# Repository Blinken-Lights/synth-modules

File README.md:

# synth-modules
Synth module schematics and code

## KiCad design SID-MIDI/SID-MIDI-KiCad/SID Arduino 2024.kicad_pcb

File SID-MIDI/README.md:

Schematic and Arduino code to integrate a SID chip with MIDI notes and CC commands for all parameters.

The schematic is intended for Eurorack, so it uses a ±12V dual supply, and boosts the SID audio output to just over ±5V, Eurorack standard levels. With some modification, this project could be used as the basis for controlling a SID in whatever context you need.

The physical controls (3 knobs and a switch) are basic, because the SID takes up a lot of pins on the Arduino, which doesn't leave many pins available for controls. But you could build a much larger controller and send data to the Arduino via MIDI, or by changing the code, you could increase the serial speed to 250000 baud and send control data even faster.

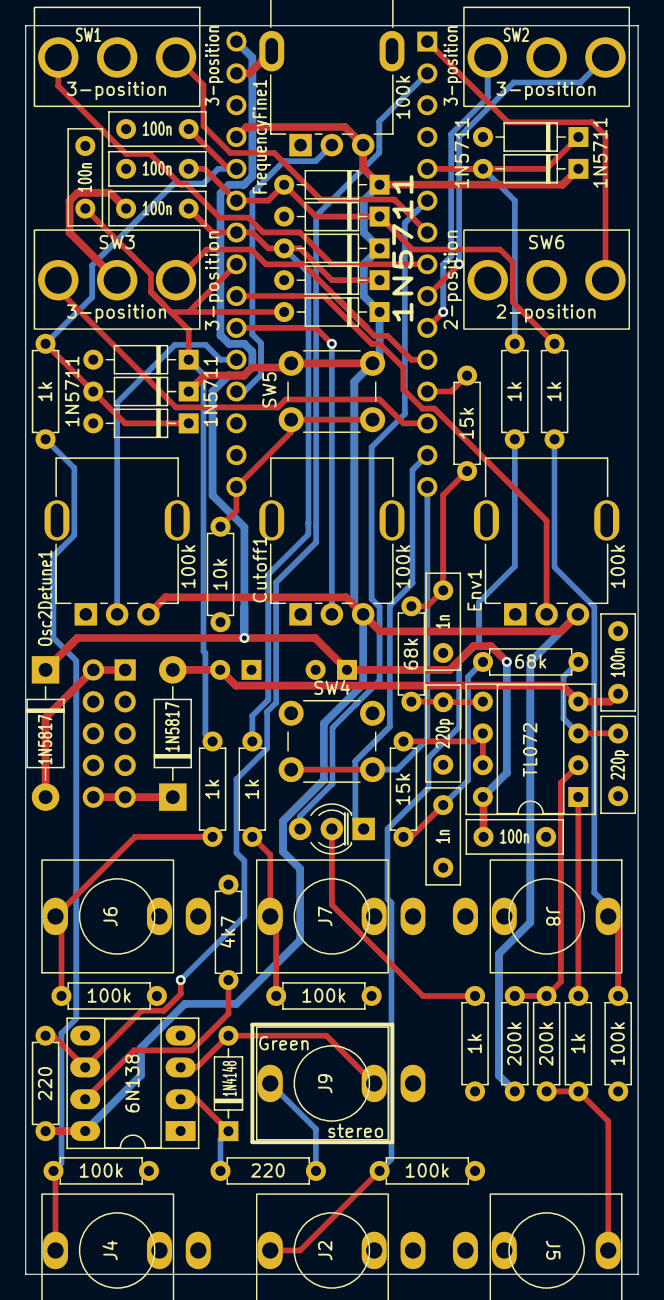
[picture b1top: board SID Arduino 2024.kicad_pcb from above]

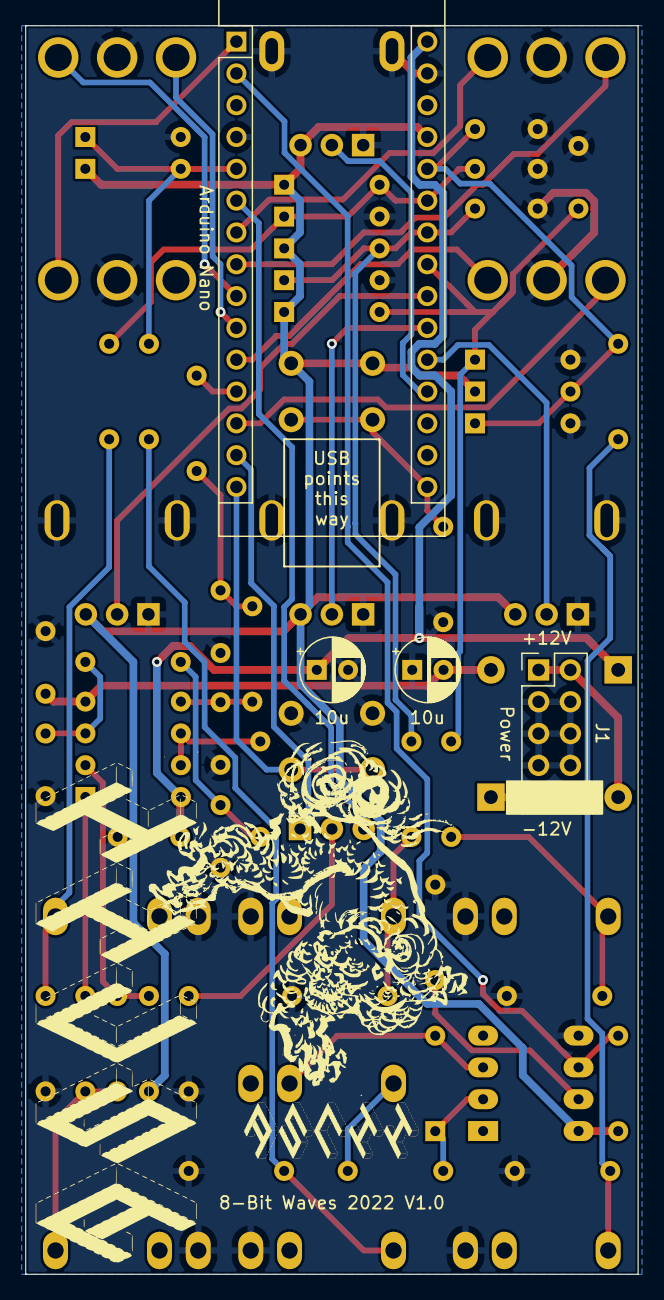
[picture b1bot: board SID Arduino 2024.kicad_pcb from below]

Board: 2 copper layers, 48.9 x 99.7 mm, 69 parts (4 on the bottom side), 46 nets.

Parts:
A1: Arduino_Nano_v3.x; Arduino_Nano
C1, C2: 10u; CP_Radial_D5.0mm_P2.50mm
C3, C4, C7, C8, C9, C10: 100n; C_Disc_D7.5mm_W2.5mm_P5.00mm
C5, C11: 1n; C_Disc_D7.5mm_W2.5mm_P5.00mm
C6, C12: 220p; C_Disc_D7.5mm_W2.5mm_P5.00mm
Cutoff1: 100k; Potentiometer_GND_Alpha_RD901F-40-00D_Single_Vertical_OvalH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
D1, D2: 1N5817; D_DO-41_SOD81_P10.16mm_Horizontal
D3, D4, D8, D9, D10, D11, D12, D13, D14, D15: 1N5711; D_DO-35_SOD27_P7.62mm_Horizontal
D16: 1N4148; D_DO-35_SOD27_P7.62mm_HorizontalVal
D17: Status; LED_D3.0mm-3
Env1: 100k; Potentiometer_GND_Alpha_RD901F-40-00D_Single_Vertical_OvalH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
FrequencyFine1: 100k; Potentiometer_GND_Alpha_RD901F-40-00D_Single_Vertical_OvalH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
J1: Power; PinHeader_2x05_P2.54mm_Vertical
J2: Clk; Thonkiconn
J4: 1V/Oct; Thonkiconn
J5: Audio; Thonkiconn
J6: Detune; Thonkiconn
J7: Cutoff; Thonkiconn
J8: Envelope; Thonkiconn
J9: MIDI; Thonkiconn
Osc2Detune1: 100k; Potentiometer_GND_Alpha_RD901F-40-00D_Single_Vertical_OvalH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
R1, R7, R13, R14, R15: 100k; R_Axial_DIN0207_L6.3mm_D2.5mm_P7.62mm_Horizontal
R2: 10k; R_Axial_DIN0207_L6.3mm_D2.5mm_P7.62mm_Horizontal
R3, R9, R11, R16, R17, R18, R22: 1k; R_Axial_DIN0207_L6.3mm_D2.5mm_P7.62mm_Horizontal
R6, R23: 15k; R_Axial_DIN0207_L6.3mm_D2.5mm_P7.62mm_Horizontal
R8, R24: 68k; R_Axial_DIN0207_L6.3mm_D2.5mm_P7.62mm_Horizontal
R10, R12: 200k; R_Axial_DIN0207_L6.3mm_D2.5mm_P7.62mm_Horizontal
R19, R21: 220; R_Axial_DIN0207_L6.3mm_D2.5mm_P7.62mm_Horizontal
R20: 4k7; R_Axial_DIN0207_L6.3mm_D2.5mm_P7.62mm_Horizontal
SW1: Wave1; toggle switch
SW2: Wave2; toggle switch
SW3: Mix; toggle switch
SW4: Clk; SW_PUSH_6mm
SW5: Learn; SW_PUSH_6mm
SW6: Arp/Sync Type; toggle switch
U1: TL072; DIP-8_W7.62mm_Socket
U2: 6N138; DIP-8_W7.62mm_Socket_LongPads

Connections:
1V/Oct: A1.26 (A7), C7.1, D8.2 (A), D9.1 (K), R9.1
+5V: A1.27 (+5V), Cutoff1.3, D3.1 (K), D8.1 (K), D10.1 (K), D12.1 (K), D14.1 (K), Env1.3, FrequencyFine1.3, Osc2Detune1.3, R10.1, R21.2, SW5.1, U2.8 (VCC)
+12V: A1.30 (VIN), C1.1, C3.1, D1.1 (K), U1.8 (V+)
-12V: C2.2, C4.2, D2.2 (A), U1.4 (V-)
A0: A1.19 (A0), FrequencyFine1.2
A1: A1.20 (A1), Osc2Detune1.2
A2: A1.21 (A2), Cutoff1.2
A3: A1.22 (A3), Env1.2
A4: A1.23 (A4), C8.1, D10.2 (A), D11.1 (K), R16.1
A5: A1.24 (A5), C9.1, D12.2 (A), D13.1 (K), R17.1
A6: A1.25 (A6), C10.1, D14.2 (A), D15.1 (K), R18.1
Arp/Sync Type: A1.1 (D1/TX), SW6.1 (A)
CLK_BUTTON: A1.15 (D12), SW4.2
CLK_IN: A1.5 (D2), D3.2 (A), D4.1 (K), R3.1
GND: A1.4 (GND), A1.29 (GND), C1.2, C2.1, C3.2, C4.1, C5.1, C6.1, C7.2, C8.2, C9.2, C10.2, C11.1, C12.1, Cutoff1.1, Cutoff1.4 (GND), D4.2 (A), D9.2 (A), D11.2 (A), D13.2 (A), D15.2 (A), Env1.1, Env1.4 (GND), FrequencyFine1.1, FrequencyFine1.4 (GND), J1.3, J1.4, J1.5, J1.6, J1.7, J1.8, J2.1, J4.1, J5.1, J6.1, J7.1, J8.1, Osc2Detune1.1, Osc2Detune1.4 (GND), R1.2, R2.1, R7.2, R13.2, R14.2, R15.2, R20.2, R22.2, SW1.2 (B), SW2.2 (B), SW3.2 (B), SW4.1, SW6.2 (B), U2.5 (GND)
LEARN_BUTTON: A1.16 (D13), R2.2, SW5.2
MIDI RX: A1.2 (D0/RX), R21.1, U2.6 (VO2)
Mix0: A1.11 (D8), SW3.1 (A)
Mix1: A1.13 (D10), SW3.3 (C)
unnamed: C5.2, R6.2, R8.1
unnamed: C6.2, R8.2, U1.3 (+)
unnamed: C11.2, R23.2, R24.1
unnamed: C12.2, R24.2, U1.5 (+)
unnamed: D1.2 (A), J1.1, J1.2
unnamed: D2.1 (K), J1.9, J1.10
unnamed: D16.1 (K), R19.2, U2.2 (C1)
unnamed: D16.2 (A), J9.2, U2.3 (C2)
unnamed: D17.2 (K), R22.1
unnamed: J2.3, R1.1, R3.2
unnamed: J4.3, R7.1, R9.2
unnamed: J5.3, R11.2, R12.2
unnamed: J6.3, R13.1, R16.2
unnamed: J7.3, R14.1, R17.2
unnamed: J8.3, R15.1, R18.2
unnamed: J9.3, R19.1
unnamed: R6.1, U1.6 (-), U1.7
unnamed: R10.2, R12.1, U1.2 (-)
unnamed: R11.1, U1.1
unnamed: R20.1, U2.7 (VO1)
PWM: A1.12 (D9), R23.1
StatusBlue: A1.14 (D11), D17.1 (A1)
StatusRed: A1.6 (D3), D17.3 (A2)
Wave1-0: A1.7 (D4), SW1.1 (A)
Wave1-1: A1.8 (D5), SW1.3 (C)
Wave2-0: A1.9 (D6), SW2.1 (A)
Wave2-1: A1.10 (D7), SW2.3 (C)

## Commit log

2020-05-17 Create Meter.ino
    dependency: https://github.com/olikraus/u8glib
2020-05-17 Add files via upload
    Eagle schematic for Meter MIDI sequencer
2020-05-17 Rename STM32 MIDI Expansion.sch to MIDI-daughter-board.sch
2020-05-17 Rename LFO used in rack.sch to LFO-Complex.sch
2022-02-11 Add files via upload
    Add reverse protection diodes to input indicator LEDs
2024-02-08 Add files via upload
    Add capacity for 8 inputs
2024-02-21 Change amplification resistor to 1k8 to avoid clipping
2025-01-17 Create PicoCVAndGates
2025-01-17 Rename PicoCVAndGates to PicoCVAndGates.ino
2025-03-06 Add files via upload
    Upgraded wavetables to 1024 entries long. This reduces the amplitude differences between steps in waves which makes them sound smoother. Also improved the sync feature to make waves slower than one s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
